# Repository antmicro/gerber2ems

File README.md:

# gerber2ems - openEMS simulation based on Gerber files

Copyright (c) 2023-2026 [Antmicro](https://www.antmicro.com)

This project is a Python script that aims to streamline signal integrity simulations using open source tools.
It takes PCB production files as input (Gerber, drill files, stackup information) and simulates trace SI performance using [openEMS](https://github.com/thliebig/openEMS-Project/) - a free and open source electromagnetic field solver that uses the FDTD method.

## Installation

### [OpenEMS](https://www.openems.de/)

Install the following packages (on Debian/Ubuntu):

```bash
sudo apt update
sudo apt install build-essential cmake git libhdf5-dev libvtk9-dev libboost-all-dev libcgal-dev libtinyxml-dev qtbase5-dev libvtk9-qt-dev cython3 pip
```

Clone the repository, compile and install openEMS:

It is recommended to use the stable v0.37.0 version of OpenEMS, as this is the latest one tested with gerber2ems.
```bash
git clone https://github.com/thliebig/openEMS-Project.git
pushd ./openEMS-Project
git checkout v0.37.0
git submodule update --init --recursive
./update_openEMS.sh ~/opt/openEMS --python
popd
```

### Script installation

1. Install the dependencies:
```bash
sudo apt install gerbv python3
```

2. Clone and install gerber2ems
```bash
git clone https://github.com/antmicro/gerber2ems.git
pushd ./gerber2ems
source ~/opt/openEMS/venv/bin/activate
pip install .
ln -s ~/opt/openEMS/venv/bin/{gerber2ems,ems2paraview,ems2png} ~/.local/bin
popd
```

> [!NOTE]
> I you want to use `ems2paraview` command run also `sudo apt install paraview python3-paraview`.

You can test `gerber2ems` with built-in examples.
The examples are slices of our open hardware [Signal Integrity Test Board](https://openhardware.antmicro.com/boards/si-simulation-test-board/), which were generated using the [KiCad SI wrapper](https://github.com/antmicro/kicad-si-simulation-wrapper).
Selected examples contain VNA measurements in dedicated vna.csv files, which allows us to compare openEMS simulation results with real life measurements.
```bash
cd ./gerber2ems/examples/stub_short
gerber2ems -a
```

### Container usage

Alternatively `gerber2ems` can be run using container definition from this repository

```bash
docker build -t gerber2ems .
docker run -w "$PWD" --mount type=bind,source="$PWD",target="$PWD" gerber2ems -a
```

## Usage

For quick lookup, use `gerber2ems --help`.

To simulate a trace, follow these steps:

* Prepare input files and put them in the `fab/` folder (described in detail in the [PCB Input File Preparation section](#pcb-input-files-preparation))
* Prepare the config `simulation.json` file (described in detail in the [Config Preparation section](#config-preparation))
* Run `gerber2ems -a` (process described in the [Geometry Creation section](#geometry-creation))
* View the results in `ems/results` (described in detail in the [Results section](#results))
* Run `gerber2ems -a --export-field` and use Paraview to view an animation of the E-field (described in detail in the [Paraview section](#paraview))

## Results

The simulation output of the `stub_short` example is shown below.
This software returns the following types of output:

### S-parameter and impedance data

Impedance and S-parameter data gathered during the simulations, stored in CSV format with a header.

### S-parameter chart

Plot of each S-parameter measured during each excitation.

### Smith chart

Plot of parameter S-11 for each excitation.

### Impedance chart

Plot of each excited port vs. frequency.

The `stub_short` example contains a `vna.csv` file, which can be used to verify simulation results.

## How it works

### Project preparation

Simulating an entire PCB is extremely resource-intensive, so it is important to separate a region of interest as small in size as possible - unneeded traces, pours etc., should be removed. 
If entire layers are redundant, you can remove them in later steps.

Ports of interest should be marked by a virtual component in positions files. Their designator should begin with "SP" and be followed by port number. 

Origin point for drill files should be placed in bottom-left corner.

Every trace or pour that is somehow terminated in reality and will exist in the simulation should also be terminated using a simulation port or connected to ground.

For now, capacitors are not simulated and, for high frequency simulation, they can be aproximated by shorting them using a trace.

### PCB input file preparation

This script requires multiple input files for geometry creation. 
They should all reside in the "fab" folder and are listed below:

* Gerber files - each simulated copper layer should have a corresponding Gerber file named in the following format: "\<optional-text\>-\<name-from-stackup-file\>.gbr"

* Stackup file - a file describing the PCB stackup, named "stackup.json". 
Example format:

    ```
    {
        "layers": [
            {
                "name": "F.Cu",
                "type": "copper",
                "color": null,
                "thickness": 0.035,
                "material": null,
                "epsilon": null,
                "lossTangent": null
            },
            {
                "name": "dielectric 1",
                "type": "core",
                "color": null,
                "thickness": 0.2,
                "material": "FR4",
                "epsilon": 4.5,
                "lossTangent": 0.02
            }
        ],
        "format_version": "1.0"
    }
    ```

* Drill file - Drill file in excellon format with plated through-holes.
Filename should end with "-PTH.drl"

* Position file - File describing positions of ports.
  * Filename should end with "-pos.csv"
  * For vertical ports coordinates should be given with origin placed at center of pad
  * For MSL ports coordinates should be given with origin placed at center far edge of pad
  * (For MSL) The area of the port is calculated using the formulas in the table below, based on the `Width` and `Length` values from the `simulation.json` file:

    | Rotation [°] | `X` span                       | `Y` span                       | Wave travel direction |
    | ------------ | ------------------------------ | ------------------------------ | --------------------- |
    | 0            | `(PosX-Width/2, PosX+Width/2)` | `(PosY, PosY+Length)`          | Along `Y`             |
    | 90           | `(PosX-Length, PosX)`          | `(PosY-Width/2, PosY+Width/2)` | Opposite to `X`       |
    | 180          | `(PosX-Width/2, PosX+Width/2)` | `(PosY-Length, PosY)`          | Opposite to `Y`       |
    | 270          | `(PosX, PosX+Length)`          | `(PosY-Width/2, PosY+Width/2)` | Along `X`             |

  * Example file:

    ```
    # Ref     Val              Package                PosX       PosY       Rot  Side
    SP1       Simulation_Port  Simulation_Port      3.0000    11.7500  180.0000  top
    ```

### Config preparation

The `simulation.json` file configures the entire simulation. 
You can find sample files in the `example_gerbers` folder. 
All dimensions in this file are specified in **micrometers**. 
This config file consists of three sections:

#### Miscellaneous

* `format_version` - specifies the format of the config file
When writing a new config, it should be the newest supported version (visible in the `constants.py` file)
* `frequency` - `start` specifies the lowest frequency of interest and `stop` the highest (in Hz)
* `max_steps` - max number of simulation steps after which the simulation will stop unconditionally
* `sim_length` - sets `max_steps` so that simulation will last `n` times excitation signal length
* `pixel_size` - size of pixel in microns. Used during gerber conversion (default: 5) (due to a limitation of libcairo, this needs to be increased for larger boards, but try to keep as low as possible)
* `via/plating_thickness` - via plating thickness (micrometers)
* `via/filling_epsilon` - dielectric constant of the material the vias are filled in with
If they are not filled in, it should be 1

#### Grid

* `inter_layers` - number of grid lines in Z axis between neighboring PCB layers (default: 4)
* `optimal` - basic mesh grid pitch (micrometers) (used for cells on metal edge) (default: 50) (Hint: Reduce for fine detailed designs)
* `diagonal` - mesh grid pitch (micrometers) (used for regions with diagonal paths) (default: 50)
* `perpendicular` - mesh grid pitch (micrometers) (used for regions with paths perpendicular to grid) (default: 200)
* `max` - maximum mesh grid pitch (micrometers) (used outside of the board area) (default: 500)
* `cell_ratio/xy` - optimal neighboring cell size ratio (X/Y axis) (default: 1.2)
* `cell_ratio/xy` - optimal neighboring cell size ratio (Z axis) (default: 1.5)
* `margin/xy` - margin size in X/Y axis (micrometers) (how far beyond pcb the grid spreads) (default: 1500)
* `margin/z` - margin size in Z axis (micrometers) (default: 2000) (Hint: Increase for designs with wide features or ports or tall ports)
* `margin/from_trace` - Limit simulation space based on nets-of-interest bounding box (default: True) (if False, board b-box is used).

Grid pitch options should follow `optimal`<=`diagonal`<=`perpendicular`<=`max`<=`λmin/10`

#### Ports

`ports` is a list of ports. Each port has the following parameters:

* `width` - width of the port (micrometers)
* `length` - length of the port (ports are currently composed of microstripline fragments whose length should be at least 8x mesh cell size) (micrometers)
* `impedance` - terminating impedance of the port (impedance of driver or receiver) (Ohms)
* `layer` - the number of the copper layer where the port is located (counting from the top)
* `plane` - the number of the copper layer where the reference plane of the microstrip is located (counting from the top)
* `excite` - whether the simulator should use this port as an input port (for multiple excited ports, they will be excited in separate simulations).

#### differential_pairs/traces

`differential_pairs`/`traces` are lists of simulated signals. Each signal can have following fields:

* `start_p`, `stop_p`, `start_n`, `stop_n` - port numbers used for signal (differential_pair)
* `start`, `stop` - port numbers used for signal (single ended trace)
* `name` - optional name that allows to identify the signal
* `nets` - list of nets to be included during grid generation (e.g. `["/CSI_A_CLK_N","/CSI_A_CLK_P"]`). If not specified, data from `netinfo.json` file will be used. In case the file is also not present, all nets (except GND) will be considered during grid generation.  

### Geometry creation

This is an automatic step commenced with the `-g` flag.
The script locates all the files needed for creating the geometry (Gerbers, drill files, pnp files, stackup file, simulation config file).
Then it converts Gerber files to PNG using gerbv.
The PNG's are then processed into triangles and input into the geometry.
This also adds via geometries as well as port geometries.
Everything is placed on correct Z heights using the stackup file.

You can view the generated geometry, which is saved to `ems/geometry/geometry.xml`, using AppCSXCAD (installed during openEMS installation).

### Simulation

This is an automatic step commenced with the `-s` flag.
The script loads the geometry and config files. 
It inputs all the information into the engine and starts the simulations, iterating over every excited port.

At this step, the user should verify if the indicated number of timesteps is sufficient. 
The engine recommends that it should be at least 3x as long as the pulse:

    ```
    Excitation signal length is: 3211 timesteps (3.18343e-10s)
    Max. number of timesteps: 10000 ( --> 3.11429 * Excitation signal length)
    ```

The simulator converts the geometry into voxels and starts solving Maxwell equations for each edge in the mesh.
It does that for a number of timesteps (maximum number specified in config) and then exits.
For each timestep, electric field data from planes between copper planes is saved to files in the `ems/simulation` folder. Port voltage and current data is also saved.

During the simulation, one of the ports is excited using a gaussian pulse (wideband frequency content).
This pulse traverses the network and exits using ports (it can also get emitted outside the board). 

You can monitor the simulation by looking at the engine output:

    ```
    [@ 20s] Timestep: 4620 || Speed:  294.4 MC/s (3.372e-03 s/TS) || Energy: ~4.16e-16 (- 7.15dB)
    ```
This way you can see:
* what timestep you are on
* how many mesh voxels per second the simulator processes 
* how much energy is left in the system

The energy should drop during the simulation as it exits through the ports (after the excitation pulse ends), however due to inaccuracies and energy radiated it won't drop to 0.

After the simulation finishes, the user can verify the data using `Paraview` (described in a [section below](#paraview)).

### Postprocessing

This is an automatic step commenced with the `-p` flag.
The script loads simulation data for each excited port. 
It then computes an FFT to get data in the frequency domain. 
It then converts the incident and reflected wave data to impedance and S parameters. 
These are saved in CSV format in the `ems/results/S-parameters` folder. 
This data is also automatically plotted and the plots are saved to `ems/results`.

## Paraview

To view simulation data in Paraview, follow these steps:

* Run `gerber2ems -a --export-field <dump locations>`
* Run `ems2paraview <port>`

`<port>` is a simulated port number, defined in the `simulation.json`,
to list all available ports use: `ems2paraview -l`

`dump locations` can be skipped (dump at all possible locations), or you can choose one or more keywords from the following list:

* `outer` - dump a field 100 um above the board surface
* `cu-outer` - dump a field on the outer cooper Z-position
* `cu-inner` - dump a field on the inner cooper Z-position
* `substrate` - dump a field in the middle of each dielectric layer

`--oversampling <int num>` - can be added to increase the frequency of exporting fields (normally OpenEMS dumps a field once per few hundreds timesteps) (`<int num>` defaults to 4)

> [!WARNING]  
> Field exports can easily take hundreds GB of storage

## Animation

To generate an animation:

1. Generate a PCB blend model (See [picknblend](https://antmicro.github.io/picknblend/quickstart.html))
2. Run `gerber2ems` with the `--export-field` flag and increased oversampling (`--oversampling 16`) (See the [Paraview section](#paraview))
3. Convert the generated `*.vtr` files to grayscale pngs (run `ems2png`)
4. Open the PCB blend in `blender` and append [EMS_Plane](EMS_Plane.blend) (`File`>>`Append..`>>`EMS_Plane.blend/Object/EMS_Plane`)
5. Set plane dimensions (it should be roughly the same as the slice size)
6. Enter the `Shading` workspace
7. In each texture node on the left, click the folder icon and select a png generated in the third step with the lowest number (e.g. `simulation_images/e_field_0_0000` for the first trace, `simulation_images/e_field_1_0000` for the second).
8. If the animation should show only a single trace, substitute one texture node with an RGB node set to black
9. On texture nodes, change source type from `Single Image` to `Image Sequence` and update the `Frames` field with the number of images generated for the corresponding trace
10. Set view mode to `rendered` and position `EMS_Plane` just above the corresponding trace on the PCB texture (you may want to switch to a frame where the field is stronger and covers most of the trace)
11. Select `EMS_Plane` and apply any type of keyframe on the first and last frame of the image sequence
12. In `blendcfg.yaml` add a new preset:

    ```yaml
    ems_animation:
    CAMERAS:
        PHOTO1: true
    POSITIONS:
        TOP: true
    RENDERER:
        FPS: 25
    SCENE:
        RENDERED_OBJECT: Object/EMS_Plane
    OUTPUTS:
        - ANIMATION:
    ```

13. Run `pcbooth -b <PCB_name>.blend -c ems_animation`

Sample animation:

| Top side                                             | Bottom side                                             |
| ---------------------------------------------------- | ------------------------------------------------------- |
|  |  |

> [!TIP]
> Consider creating a new blend file instead of simply using the output of `picknblend`. In this new file add the `picknblend` output as a linked blender model. This will allow you to reuse the base blender model for showing different trace simulations and will prevent accidental refresh by `gerber2blend`/`picknblend`.

## Licensing

This project is published under the [Apache-2.0](LICENSE) license.

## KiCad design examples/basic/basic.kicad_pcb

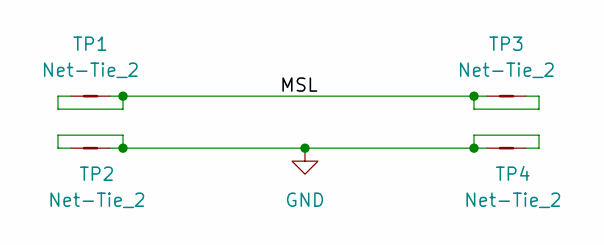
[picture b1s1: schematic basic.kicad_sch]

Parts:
TP1, TP2, TP3, TP4: Net-Tie_2; NetTie-2_SMD_Pad0.127mm

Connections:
/MSL: TP1.1, TP1.2, TP3.1, TP3.2
GND: TP2.1, TP2.2, TP4.1, TP4.2

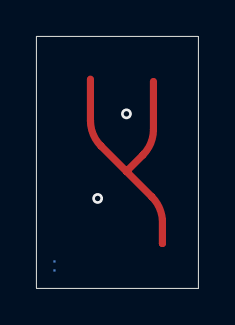
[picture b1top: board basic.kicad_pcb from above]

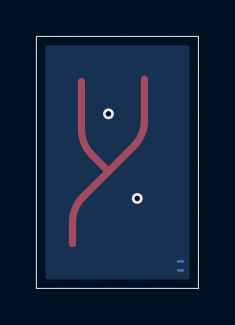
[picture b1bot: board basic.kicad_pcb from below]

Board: 2 copper layers, 9.0 x 14.0 mm, 7 parts (2 on the bottom side), 2 nets.

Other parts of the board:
SP1, SP2, SP3: Simulation_Port

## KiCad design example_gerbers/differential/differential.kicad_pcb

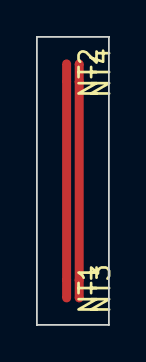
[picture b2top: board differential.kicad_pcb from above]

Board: 2 copper layers, 4.0 x 16.0 mm, 8 parts (0 on the bottom side), 2 nets.

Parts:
NT1, NT2, NT3, NT4: NetTie_2; NetTie-2_SMD_Pad0.5mm
SP1, SP2, SP3, SP4: Simulation_Port

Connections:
/A_+: NT1.1, NT2.2
/A_-: NT3.1, NT4.2

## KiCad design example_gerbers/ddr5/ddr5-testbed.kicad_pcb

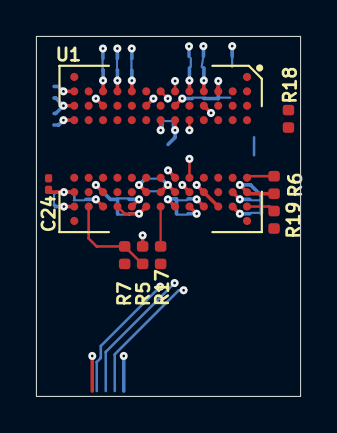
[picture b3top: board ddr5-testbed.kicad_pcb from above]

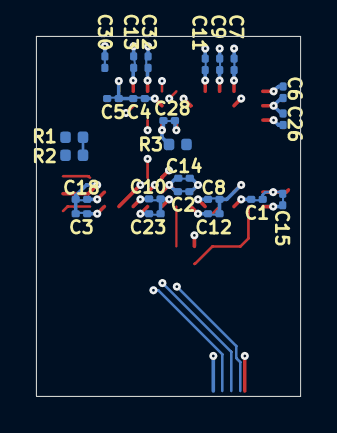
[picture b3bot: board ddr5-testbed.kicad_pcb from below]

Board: 6 copper layers, 14.7 x 20.0 mm, 38 parts (24 on the bottom side), 11 nets.

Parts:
C1, C2, C3, C4, C5, C6, C7, C8, C9, C10, C11, C12, C13, C14, C15, C18, C23, C24, C26, C28, C30, C32: C_100n_0201; 0201-res
R1, R5: R_1k_0402; 0402-res
R2, R7, R17, R18, R19: R_0R_0402; 0402-res
R3: R_10k_0402; 0402-res
R6: R_240R_1%_0402; 0402-res
SP1, SP2, SP3, SP4, SP5, SP6: Simulation-Port
U1: MT60B2G8HB-48B_A; FVBGA-82_11x13_9.0x11.0mm

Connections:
/DDR5/R_LBDQ: R18.1, U1.A2 (LBDQ)
/DDR5/R_LBDQS: R19.1, U1.A10 (LBDQS)
/DDR5/R_ODT_CA_A: R1.2, R2.1, U1.G2 (CA_ODT)
/DDR5/R_RESET_N: R5.2, R7.1, U1.M10 (RESET_N)
/DDR5/R_TEN: R17.1, U1.G10 (TEN)
/DDR5/ZQ: R6.1, U1.A8 (ZQ)
CS_N: R3.1, U1.H4 (CS_N)
GND: C1.2, C2.2, C3.2, C4.2, C5.2, C6.2, C7.2, C8.2, C9.2, C10.2, C11.2, C12.2, C13.2, C14.2, C15.2, C18.2, C23.2, C24.2, C26.2, C28.2, C30.2, C32.2, R3.2, R6.2, U1.A3 (VSS), U1.A9 (VSS), U1.C2 (VSS), U1.C10 (VSS), U1.D3 (VSS), U1.D9 (VSS), U1.F2 (VSS), U1.F4 (VSS), U1.F8 (VSS), U1.F10 (VSS), U1.H3 (VSS), U1.H9 (VSS), U1.L3 (VSS), U1.L9 (VSS), U1.N3 (VSS), U1.N9 (VSS)
VDD: C3.1, C6.1, C9.1, C12.1, C15.1, C23.1, C26.1, C28.1, C30.1, C32.1, U1.B2 (VDD), U1.B10 (VDD), U1.E2 (VDD), U1.E10 (VDD), U1.G4 (VDD), U1.H10 (VDD), U1.K2 (VDD), U1.K10 (VDD), U1.N2 (VDD), U1.N4 (VDD), U1.N10 (VDD)
VDDQ: C1.1, C2.1, C4.1, C5.1, C7.1, C8.1, C10.1, C11.1, C13.1, C14.1, C18.1, R1.1, R5.1, U1.B3 (VDDQ), U1.B9 (VDDQ), U1.D2 (VDDQ), U1.D10 (VDDQ), U1.F3 (VDDQ), U1.F9 (VDDQ), U1.G9 (VDDQ), U1.J2 (VDDQ), U1.J10 (VDDQ), U1.L2 (VDDQ), U1.L10 (VDDQ)
VPP: C24.1, U1.A4 (VPP), U1.N8 (VPP)

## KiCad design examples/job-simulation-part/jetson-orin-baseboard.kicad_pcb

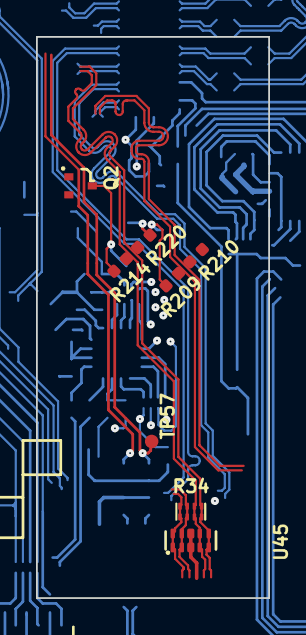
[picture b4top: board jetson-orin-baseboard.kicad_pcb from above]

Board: 8 copper layers, 12.9 x 31.2 mm, 22 parts (0 on the bottom side), 7 nets.

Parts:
Q2: PJE138K; SOT-523
R34: R_4x0R_0201_array; R_Array_4x0201_Panasonic_EXB18V
R209, R210, R214, R220: R_499R_0402; R_0402_1005Metric
SP1, SP2, SP3, SP4, SP5, SP6, SP7, SP8, SP9, SP10, SP11, SP12, SP13, SP14: Simulation_Port
TP57: TP_0.75mm_SMD; TP_SMD_0.75mm
U45: TPD4E05U06QDQARQ1; USON-10_2.5x1mm_P0.5mm

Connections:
/HDMI/HDMI_CLK_CONN_N: R34.1 (R1.1), U45.1, U45.10
/HDMI/HDMI_CLK_CONN_P: R34.2 (R2.1), U45.2, U45.9
/HDMI/HDMI_D0_CONN_N: R34.3 (R3.1), U45.4, U45.7
/HDMI/HDMI_D0_CONN_P: R34.4 (R4.1), U45.5, U45.6
/HDMI/HDMI_D0_N: R34.6 (R3.2), R214.2
/HDMI/HDMI_D0_P: R34.5 (R4.2), R220.2
GND: Q2.2 (S), Q2.3 (D), R209.1, R210.1, R214.1, R220.1, U45.3, U45.8

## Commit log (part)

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2023-11-16 Changed gerber import algorithm
2023-11-16 Prepared DDR5 testbed for simulation
2023-11-16 Added postprocessing
2023-11-16 Implemented automated dimension detection
2023-11-16 Fixed postprocessing right after simulation
2023-11-16 Repo cleanup
2023-11-16 Implemented running pcbmodelgen
2023-11-16 Written Setup part of readme
2023-11-16 Updated script
2023-11-16 Added pcbmodelgen install
2023-11-16 Added automatic stackup import
2023-11-16 Small fixes
2023-11-16 Added layer config parsing
2023-11-16 Fixed unwanted logging from libraries
2023-11-16 Created working python scripts
2023-11-16 Fixed adding ports in x direction
2023-11-16 Updated gitignore
2023-11-16 Port position import
2023-11-16 Removed adapter board example
2023-11-16 Updated basic example
2023-11-16 Add LICENSE
2023-11-16 Fixed bugs with stackup import
2023-11-16 Fix readme typo
2023-11-16 Fixed rotation bug
2023-11-16 Improved config
2023-11-16 Added via generator
2023-11-16 Renamed process_gbr to importer
2023-11-16 Added gerber import
2023-11-16 Refactored code
2023-11-16 Added simulation to CI
2023-11-16 Added simple excellon import
2023-11-16 Added directory cleanup
2023-11-16 Added test project
2023-11-16 Added config format version check
2023-11-16 Fixed linter errors
2023-11-16 Improved logging
2023-11-16 Added multilayer support to geometry generator
2023-11-16 Small changes
2023-11-16 Add diff pair parameter rendering
2023-11-16 Made install script more distro agnostic
2023-11-16 Add results and usage sections to README
2023-11-16 Replace install script with using pip
2023-11-16 [#51298] Minor changes
2023-11-16 Updated config versions
2023-11-16 Improve readme
2023-11-16 Fix port positioning
2023-11-16 Implement kmake helper
2023-11-16 Added logging to kmake calls
2023-11-16 Freezed matplotlib version
2023-11-16 Added apt_packages.list
2023-11-16 Implement config for traces
2023-11-16 Working real test case
2023-11-16 Clarify info about simulation ports
2023-11-16 Updated simulation.json in example
2023-11-16 Removed kmake step
2023-11-16 Fixed README formatting
2023-11-16 [#50036] change opencv-python to opencv-python-headless
2023-11-16 Remove report generation stub (moved to branch)
2023-11-16 Add trace length calculation for diff pairs
2023-11-16 Added support for multiple excitation
2023-11-16 Added helper kmake interface
2023-11-16 Fix minor bugs
2023-11-16 Mitigate openems locale bug
2023-11-16 Implement multiple excitation postprocessing
2023-11-16 More optimization for ddr5 example
2023-11-16 Changed required packages
2023-11-16 Fix wrong via position calculation
2023-11-16 Move trace delay calculation ealier
2023-11-16 Dependency fix
2023-11-16 Changed python package version
2023-11-16 Created new README for the flow
2023-11-16 Change port numbering in differential pair example
2023-11-16 Fix script invocation
2023-11-16 Fix multiple simulations
2023-11-16 Cleanup of virtual ports
2023-11-16 Add steps for virtual env to README
2023-11-16 Changed how mesh z_lines are generated
2023-11-16 Created example with diff pair
2023-11-16 Updated install script to use venv
2023-11-16 Remove accidental import
2023-11-16 Added install script
2023-11-16 Remove incorrect kmake_interface import
2023-11-16 Fix minor typing mistakes
2023-11-16 Remove imagemagic dependency
2023-11-16 Updated example files to kicad 7
2023-11-16 Fixed
2023-11-16 Updated vtk version in ci
2023-11-16 Add flag for field data export
2023-11-16 Remove other kmake references
2023-11-16 Remove opencv dependency
2023-11-16 Fix minor linting warning
2023-11-16 Add diff pair config parsing
2023-11-16 Update job example
2023-11-16 Mesh generation bug fix
2023-11-16 Repository clean-up
2023-11-16 Add example plots to readme
2023-11-16 Added missing packages
2023-11-16 Added impedance save
2023-11-16 Improve function docsstrings in importer.py
2023-11-16 Fixed trigonometry
2023-11-16 Added missing libxcb-cursor-dev library
2023-11-16 Rename project to gerber2ems
2023-11-16 Add test case from JOB
2023-11-16 Add more comments
2023-11-16 Fix port name on PCB
2023-11-16 Started work on report generation
2023-11-16 Modify pyproject to include mplstyle files
2023-11-16 Implement trace length calculation
2023-11-16 Add real test case
2023-11-16 [#51298] Review README.md
2023-11-16 Restructure repository
2023-11-16 Added linter config
2023-11-16 Add saving delays to csv
2023-11-16 Rework directory structure to be compliant with pythons packaging need
2023-11-16 Add explanations to constants.py
2023-11-16 Added antmicro theme to plots
2023-11-16 README: mention licensing
2023-11-16 Remove sentence about port orientation
2023-11-29 Improve installation process in readme
2023-12-01 Change gitignore to not ignore input files
2023-12-01 Add input files
2023-12-01 README: minor fix
2023-12-01 Add missing "sudo apt install"
2023-12-09 Appy small improvements to readme
2024-01-07 Update README.md export-field instructions
2024-01-08 README: Specify OS distro and generalize venv package
2024-03-06 [#56188] Add threads flag
2024-03-07 [#56188] Fix bug when not passing threads flag
2024-03-28 Changed import_stackup to not assume a default location, instead use a default argumetn
2024-03-29 Added some more overrideable paths in the importer.py file
2024-11-13 [#68557] Update impedance formula
2024-12-31 Add config to output image Format and DPI
    Add config where user can set output format and DPI of generated graph
2024-12-31 Save plot wrapped in function
2025-01-21 [#71940] Update copyright in README.md
2025-01-24 [#71941] Update README
2025-01-24 [#71941] Add scripts for preview
2025-01-24 [#71941] Add preview script
2025-01-24 [#71941] Change pvpython to python
2025-01-24 [#71941] Wrap preview into functions
2025-01-24 [#71941] Remove run() method
2025-01-24 [#71941] Remove images
2025-01-24 [#71941] Change arguments names
2025-01-24 [#71941] Change python path
2025-01-24 [#71941] Update get_sim_results method
2025-01-24 [#71941] Rename preview script
2025-01-24 [#71941] Rename variables in get_ports() method
2025-01-24 [#71941] Use subprocess instead of os
2025-02-11 [#70999] Remove threads option
2025-02-21 [#72726] Add Port material directly
2025-03-03 [#71336] Dynamic/targeted grid
2025-03-04 [#74026] Clarify port position in Readme
2025-03-07 Fix spelling ems2paraview
2025-03-18 [#74683] Update removal of edge.cuts from gerbers
2025-03-19 [#57057] Edit charts style
2025-03-25 [#74431] Fix passing config to multiprocessing pool
2025-03-27 [#74962] Fix metal import
2025-03-31 [#71177] Remove duplicated port position load
2025-04-02 [#72406] Update examples and readme
2025-05-12 Restrict numpy version
2025-06-09 [#78639] ems2paraview: Import data as separate fields
2025-06-09 [#78639] gerber2ems: More flexible field dumps
2025-06-09 [#78639] ems2paraview: Rescale over time & show only one data set
2025-06-09 [#78639] README review
2025-06-09 [#78639] ems2paraview: Set correct display type
2025-06-10 [#78639] gerber2ems: Fix field dump generation
2025-06-12 [#77066] Correct unit multiplication
2025-06-12 [#77066] Processs input data using multiplier
2025-06-16 [#71173] Clean EMS_Plane.blend
2025-06-16 [#71173] Add gerber2ems > blender animation guide
2025-06-16 [#71173] Add ems2png script
2025-06-16 [#71173] README review
2025-06-18 [#78810] gerber2ems -p now takes csv as input
2025-06-18 [#78810] Small corrections to graph generation
2025-06-18 [#78810] Start updating postprocessing to accept csv
2025-06-18 [#78810] Cleanup postprocessing
2025-06-20 [#78810] Add arguments for input/output path config
2025-06-25 [#78810] Add ports to simulation.json if none based on pos.csv
2025-06-25 [#78810] Silence code checks
2025-06-26 [#78810] Readme: force numpy update
2025-06-26 [#78810] Readme: minor install update
2025-06-26 [#78810] save to csv: do not use ,
2025-07-15 [#78810] Apply reviewer suggestsions
2025-07-15 [#78810] Update load_sparams error message
2025-07-15 [#78810] Update s_params legend
2025-07-23 [#79217] Correct grid generation corner case
2025-07-23 [#79217] Correct gerber parsing
2025-07-28 [#81026] Update csv header
2025-07-29 [#79607] examples: Correct simulation.json for filter
2025-07-30 [#79607] Update CI
2025-07-30 [#79607] Extend filter max_steps
2025-11-27 [#87098] Fix .png export when using NumPy 1.x
2025-12-19 [#88101] Examples: Add optional gerbers
2026-01-07 [#89417] Fix empty cooper layer import
2026-01-20 [#90057] Correct plot style consistency
2026-01-30 [#90469] Lock dependencies, update readme
2026-01-30 [#89122] Update filter example
2026-04-22 [#94973] Add Dockerfile
2026-04-23 [#94973] Readme: add docker instruction
2026-04-23 [#94973] Docker: Combine steps

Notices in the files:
parts and their libraries:
License: Apache-2.0
